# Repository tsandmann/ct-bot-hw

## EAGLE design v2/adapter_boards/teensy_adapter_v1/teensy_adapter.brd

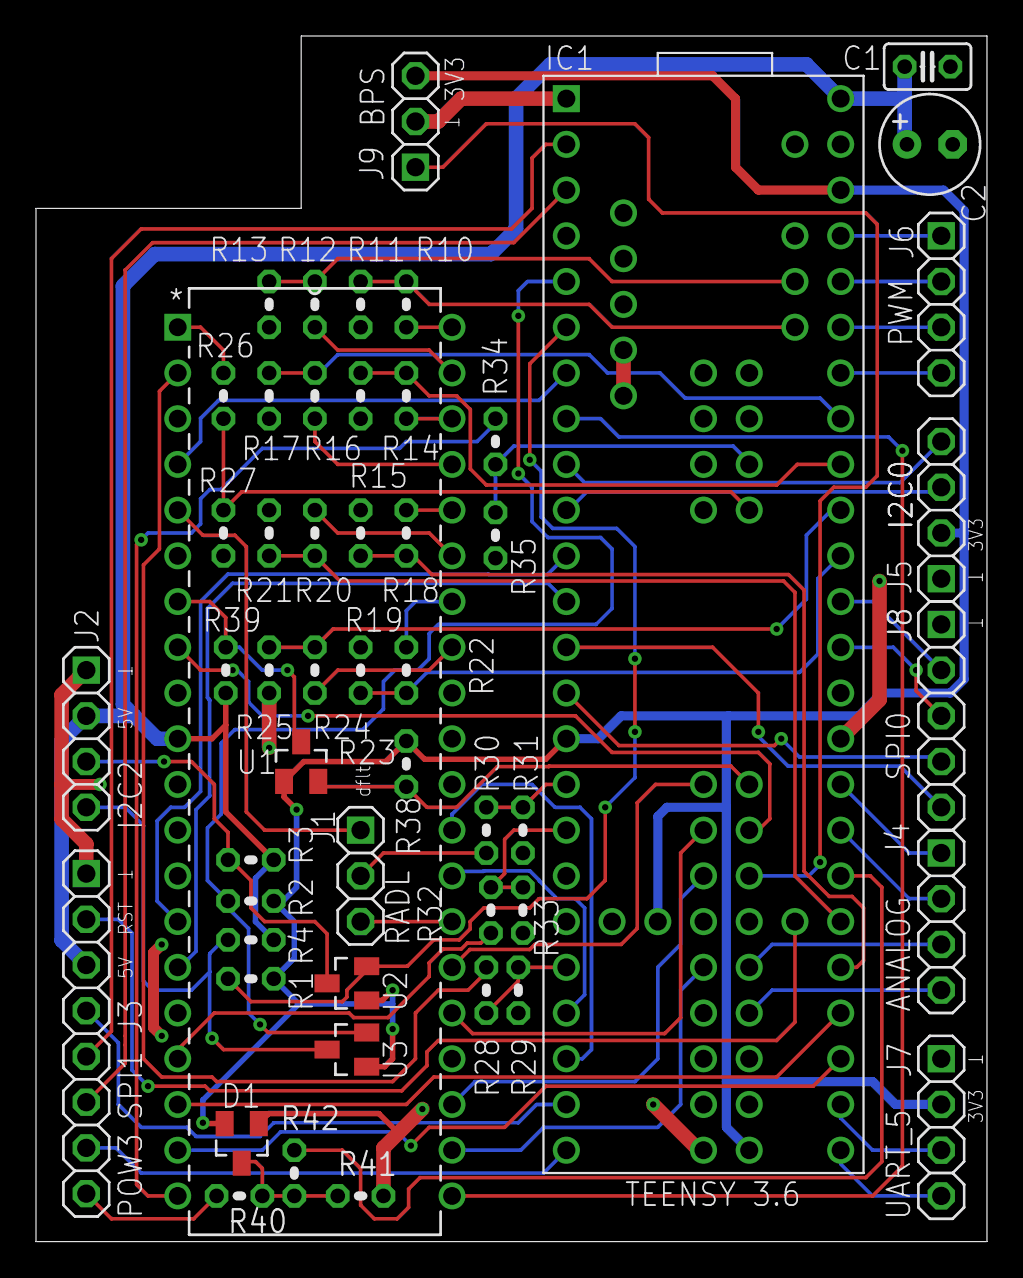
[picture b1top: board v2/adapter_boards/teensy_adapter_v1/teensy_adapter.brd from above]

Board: 2 copper layers, 52.8 x 67.0 mm, 52 parts (0 on the bottom side), 75 nets.

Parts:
C1: 100nF; C025-025X050
C2: 220uF; E2,5-6
D1: BAV99; SOT23
IC1: TEENSY 3.6; T36
IC2: ATMEGA1284P; DIP254P1524X483-40
J1: RADL; 1X03
J2: I2C_2; 1X04
J3: SPI_1; 1X08
J4: Erw_analog; 1X04
J5: I2C_0; 1X04
J6: Erw_PWM; 1X04
J7: Uart_5; 1X04
J8: SPI_0; 1X05
J9: BPS; 1X03
R1, R2, R11, R13: 4k7; 0204V
R3, R4, R38, R39: 10k; 0204V
R10, R12: 1k8; 0204V
R14, R16, R18, R20, R22, R24, R28: 0; 0204V
R15, R17, R23, R25, R26, R34, R40: 100k; 0204V
R19, R21: 820k; 0204V
R27, R35: 180k; 0204V
R29: 47k; 0204V
R30, R32: 2k2; 0204V
R31, R33: 3k9; 0204V
R41: 22k; 0204V
R42: 1k; 0204V
U1, U2, U3: BSS138

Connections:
+3V3: D1.2, IC1.3V3(1), IC1.3V3(2), IC1.3V3(3), IC1.3V3(4), J5.2, J7.2, J9.3, R1.2, R2.2, R38.1, U1.G, U2.G, U3.G
+5V: C1.1, C2.+, IC1.VIN, IC2.10, J2.2, J3.3, R3.2, R4.2, R39.1
A21_DAC0: IC1.DAC0, J4.2
A22_DAC1: IC1.DAC1, J4.1
ABSTL: IC2.40, R10.2
ABSTL_3V3: IC1.A11, R10.1, R11.1
ABSTR: IC2.39, R12.2
ABSTR_3V3: IC1.A10, R12.1, R13.1
BAT_IN_FB: IC1.39, R42.1
BPS_3V3: IC1.51, J9.1
CS0: IC1.15, J8.2
CS1: IC1.31, J3.4
CS2: IC1.43, IC2.22
FERNBED: IC2.2, R28.2
FERNBED_3V3: IC1.28, R28.1, R29.1
GND: C1.2, C2.-, D1.1, IC1.AGND, IC1.G0, IC1.G1, IC1.G2, IC1.G3, IC1.G4, IC1.G5, IC1.G6, IC2.11, IC2.31, J2.1, J3.1, J5.1, J7.1, J8.1, J9.2, R11.2, R13.2, R15.2, R17.2, R19.2, R21.2, R23.2, R25.2, R27.2, R29.2, R31.2, R33.2, R35.2, R41.2
GPIO40: IC1.40, IC2.26
GPIO41: IC1.41, IC2.25
GPIO42: IC1.42, IC2.23
KANTEL: IC2.34, R22.2
KANTEL_3V3: IC1.16, R22.1, R23.1
KANTER: IC2.33, R24.2
KANTER_3V3: IC1.17, R24.1, R25.1
KLAPPE: IC2.20, R34.2
KLAPPE_3V3: IC1.55, R34.1, R35.1
LDRL: IC2.36, R18.2
LDRL_3V3: IC1.37, R18.1, R19.1
LDRR: IC2.35, R20.2
LDRR_3V3: IC1.38, R20.1, R21.1
MAUS_CLK: IC1.52, IC2.8
MAUS_D_3V3: IC1.53, R38.2, U1.S
MISO0: IC1.12, J8.4
MISO1: IC1.1, J3.6
MLINKS: IC2.38, R14.2
MLINKS_3V3: IC1.18, R14.1, R15.1
MOSI0: IC1.11, J8.5
MOSI1: IC1.0, J3.5
MOT_L_DIR: IC1.29, IC2.28
MOT_L_PWM: IC1.35, IC2.19
MOT_R_DIR: IC1.30, IC2.29
MOT_R_PWM: IC1.36, IC2.18
MRECHTS: IC2.37, R16.2
MRECHTS_3V3: IC1.19, R16.1, R17.1
unnamed: D1.3, R40.2, R41.1, R42.2
POW3: J3.8, R40.1
PWM1: IC1.5, IC2.4
PWM2: IC1.6, IC2.21
PWM3: IC1.20, J6.4
PWM4: IC1.21, J6.3
PWM5: IC1.22, J6.2
PWM6: IC1.23, J6.1
RADL: J1.2, R30.2
RADL1: IC2.5, J1.1
RADL2: IC2.27, J1.3
RADL_3V3: IC1.24, R30.1, R31.1
RADR: IC2.17, R32.2
RADR_3V3: IC1.25, R32.1, R33.1
RESET: IC1.R, J3.2
RX2: IC1.9, IC2.14
RX5: IC1.34, J7.3
SCHRANKE: IC2.1, R26.2
SCHRANKE_3V3: IC1.54, R26.1, R27.1
SCK0: IC1.14, J8.3
SCK1: IC1.32, J3.7
SCL0: IC1.7, J5.4
SCL2: IC1.3, R2.1, U3.S
SCL2_5V: J2.4, R4.1, U3.D
SDA0: IC1.8, J5.3
SDA2: IC1.4, R1.1, U2.S
SDA2_5V: J2.3, R3.1, U2.D
SDIO_5V: IC2.7, R39.2, U1.D
SERVO2_FB: IC1.49, J4.4
SERVO3_FB: IC1.50, J4.3
TX2: IC1.10, IC2.15
TX5: IC1.33, J7.4

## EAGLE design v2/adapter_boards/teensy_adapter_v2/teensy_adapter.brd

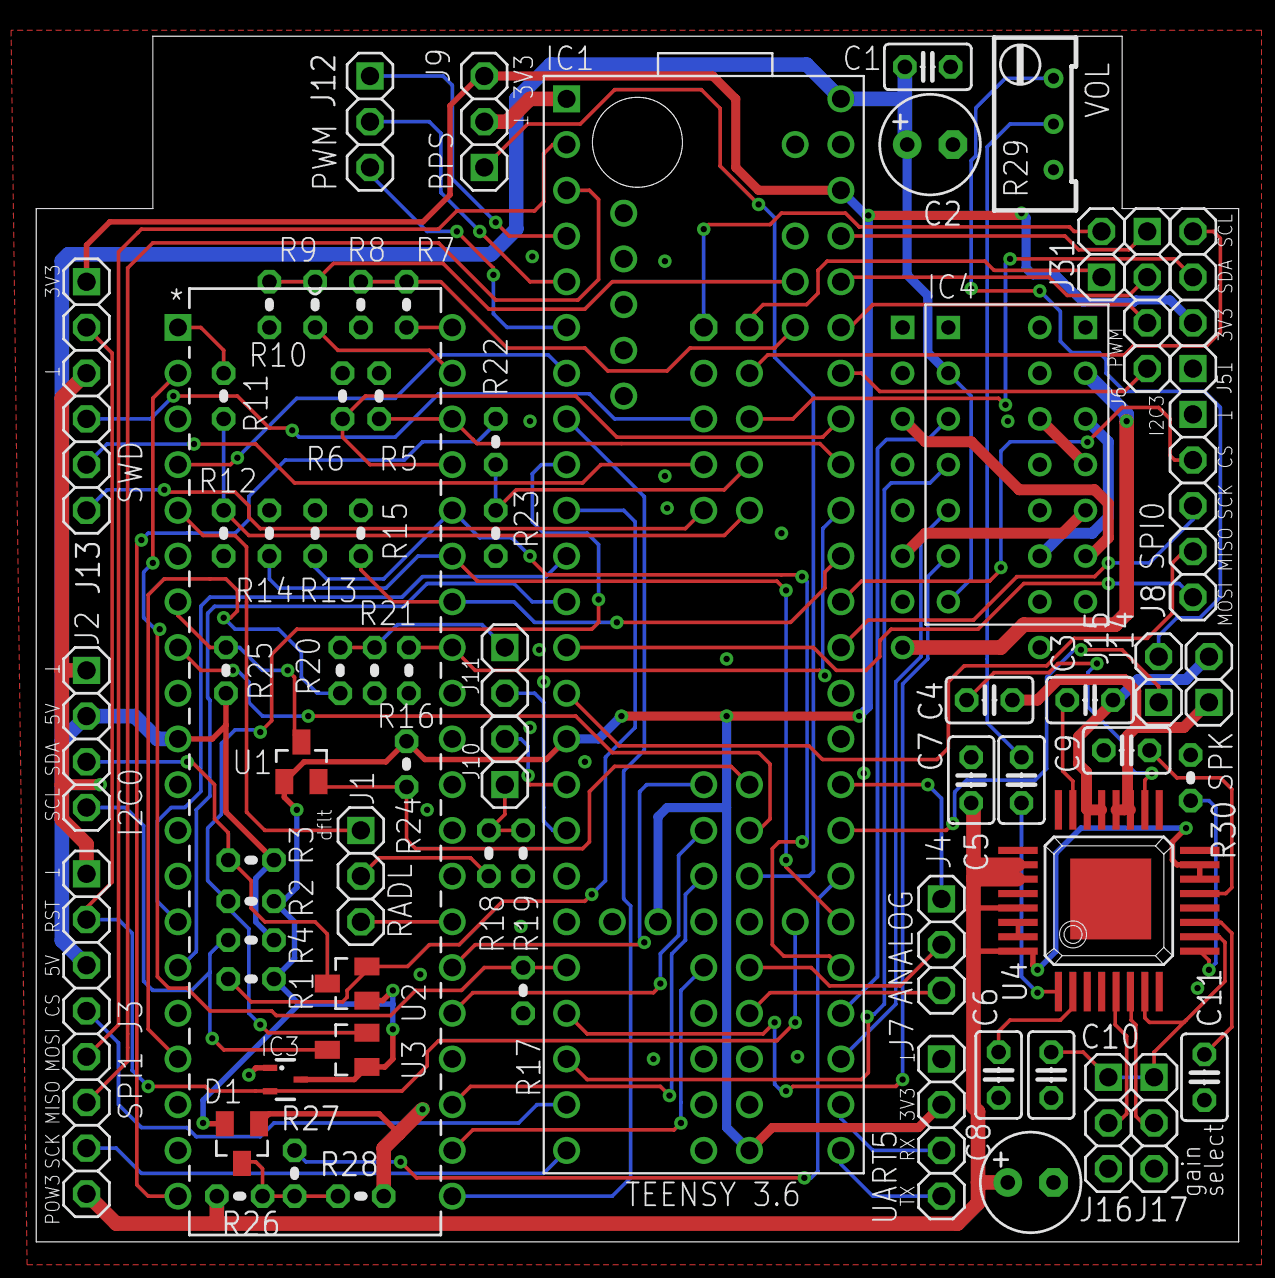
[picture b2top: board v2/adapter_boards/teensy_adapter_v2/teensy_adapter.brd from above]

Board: 2 copper layers, 66.8 x 67.0 mm, 70 parts (1 on the bottom side), 98 nets.

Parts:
C1: 100nF; C025-025X050
C2, C8: 220uF; E2,5-6
C3, C4: 220nF; C025-025X050
C5, C6, C7, C9, C11: 1uF; C025-025X050
C10: 10nF; C025-025X050
D1: BAV99; SOT23
IC1: TEENSY 3.6; T36
IC2: ATMEGA1284P; DIP254P1524X483-40
IC3: MAX803REXR; SC70-3L
IC4: DRV8835; POLOLU_MOTOR_DRV_DRV8835
IC5: L293D; DIL16
J1: RADL_SEL; 1X03
J2: I2C_0; 1X04
J3: SPI_1; 1X08
J4: Erw_analog; 1X03
J5: I2C_3; 1X04
J6: Erw_PWM_2; 1X04
J7: Uart_5; 1X04
J8: SPI_0; 1X05
J9: BPS; 1X03
J10: RADL; 1X02
J11: RADR; 1X02
J12: Erw_PWM_1; 1X03
J13: SWD; 1X06
J14: SPEAKER; 1X02
J15: AUDIO; 1X02
J16: GAIN_0; 1X03
J17: GAIN_1; 1X03
J31: SWD_KL02; 1X02
J32: SWD_KL02; 1X02/90
R1, R2, R8, R10: 4k7; 0204V
R3, R4, R24, R25: 10k; 0204V
R5, R6, R11, R15, R16, R22, R26, R30: 100k; 0204V
R7, R9: 1k8; 0204V
R12, R23: 180k; 0204V
R13, R14: 820k; 0204V
R17: 47k; 0204V
R18, R20: 2k2; 0204V
R19, R21: 3k9; 0204V
R27: 1k; 0204V
R28: 22k; 0204V
R29: 5k; RTRIM64W
U1, U2, U3: BSS138
U4: TPA3106D1; HTQFP32

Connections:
+3V3: D1.2, IC1.3V3(1), IC1.3V3(2), IC1.3V3(3), IC1.3V3(4), IC3.3, J5.2, J7.2, J9.3, J13.1, R1.2, R2.2, R24.1, U1.G, U2.G, U3.G
+5V: C1.1, C2.+, IC1.VIN, IC2.10, IC4.MODE, IC4.VCC, J2.2, J3.3, R3.2, R4.2, R25.1
+6V: IC4.VIN, IC5.8
A22_DAC1: IC1.DAC1, J4.1
ABSTL: IC2.40, R7.2
ABSTL_3V3: IC1.A11, R7.1, R8.1
ABSTR: IC2.39, R9.2
ABSTR_3V3: IC1.A10, R9.1, R10.1
AUDIO_OUT: IC1.DAC0, J15.1
BAT_IN_FB: IC1.39, R27.1
BPS_3V3: IC1.51, J9.1
BSN: C4.1, U4.18
BSP: C3.1, U4.23
CS0: IC1.15, J8.2
CS1: IC1.31, J3.4
CS2: IC1.43, IC2.22
FERNBED_3V3: IC1.28, IC2.2, R17.1
GAIN0: J16.2, U4.5
GAIN1: J17.2, U4.6
GND: C1.2, C2.-, C6.2, C7.2, C8.-, C9.2, C10.2, C11.2, D1.1, IC1.AGND, IC1.G0, IC1.G1, IC1.G2, IC1.G3, IC1.G4, IC1.G5, IC1.G6, IC2.11, IC2.31, IC3.1, IC4.LGND, IC4.MGND, J2.1, J3.1, J5.1, J7.1, J8.1, J9.2, J13.3, J16.3, J17.3, R5.2, R6.2, R8.2, R10.2, R12.2, R13.2, R14.2, R15.2, R16.2, R17.2, R19.2, R21.2, R23.2, R28.2, R29.1, R30.1, U4.3, U4.4, U4.12, U4.16, U4.17, U4.24, U4.25, U4.PAD
GPIO40: IC1.40, IC2.26
GPIO41: IC1.41, IC2.25
GPIO42: IC1.42, IC2.23
INN: C6.1, U4.2
INP: C5.1, U4.1
KANTEL_3V3: IC1.16, IC2.34, R15.1
KANTER_3V3: IC1.17, IC2.33, R16.1
KL02_DC: J31.1, J32.1
KL02_DD: J31.2, J32.2
KLAPPE: IC2.20, R22.2
KLAPPE_3V3: IC1.55, R22.1, R23.1
LDRL_3V3: IC1.37, IC2.36, R13.1
LDRR_3V3: IC1.38, IC2.35, R14.1
LINE_IN: J15.2, R29.3
MAUS_CLK: IC1.52, IC2.8
MAUS_D_3V3: IC1.53, R24.2, U1.S
MISO0: IC1.12, J8.4
MISO1: IC1.1, J3.6
MLINKS_3V3: IC1.18, IC2.38, R5.1
MOSI0: IC1.11, J8.5
MOSI1: IC1.0, J3.5
MOT_L_1: IC4.AOUT1, IC5.3
MOT_L_2: IC4.AOUT2, IC5.6
MOT_L_DIR: IC1.29, IC4.APHASE
MOT_L_PWM: IC1.35, IC4.AENBL
MOT_R_1: IC4.BOUT1, IC5.14
MOT_R_2: IC4.BOUT2, IC5.11
MOT_R_DIR: IC1.30, IC4.BPHASE
MOT_R_PWM: IC1.36, IC4.BENBL
MRECHTS_3V3: IC1.19, IC2.37, R6.1
unnamed: D1.3, R26.2, R27.2, R28.1
unnamed: U4.30, U4.31
unnamed: C5.2, R29.2
OUTN: C4.2, J14.1, U4.19, U4.20
OUTP: C3.2, J14.2, U4.21, U4.22
POW3: C7.1, C8.+, J3.8, R26.1, U4.14, U4.15, U4.26, U4.27, U4.29, U4.32
PWM1: IC1.5, IC2.4
PWM2: IC1.6, IC2.21
PWM3: IC1.20, J6.4
PWM4: IC1.21, J6.3
PWM5: IC1.22, J6.2
PWM6: IC1.23, J6.1
PWM_ERW1: IC1.2, J12.1
PWM_ERW2: IC1.3, J12.2
PWM_ERW3: IC1.4, J12.3
RADL: IC1.24, J10.2
RADL1: IC2.5, J1.1
RADL2: IC2.27, J1.3
RADL_3V3: J10.1, R18.1, R19.1
RADL_5V: J1.2, R18.2
RADR: IC1.25, J11.2
RADR_3V3: J11.1, R20.1, R21.1
RADR_5V: IC2.17, R20.2
RESET: IC1.R, IC3.2, J3.2, J13.2
ROSC: R30.2, U4.9
RX2: IC1.9, IC2.14
RX5: IC1.34, J7.3
SCHRANKE: IC2.1, R11.2
SCHRANKE_3V3: IC1.54, R11.1, R12.1
SCK0: IC1.14, J8.3
SCK1: IC1.32, J3.7
SCL0: IC1.7, R2.1, U3.S
SCL0_5V: J2.4, R4.1, U3.D
SCL3: IC1.57, J5.4
SDA0: IC1.8, R1.1, U2.S
SDA0_5V: J2.3, R3.1, U2.D
SDA3: IC1.56, J5.3
SDIO_5V: IC2.7, R25.2, U1.D
SERVO2_FB: IC1.49, J4.3
SERVO3_FB: IC1.50, J4.2
SWCLK: IC1.DC, J13.5
SWDIO: IC1.DD, J13.6
SWD_EN: IC1.DE, J13.4
TX2: IC1.10, IC2.15
TX5: IC1.33, J7.4
VBYP: C11.1, U4.11
VCLAMP: C9.1, U4.13
VREG: C10.1, J16.1, J17.1, U4.7, U4.10

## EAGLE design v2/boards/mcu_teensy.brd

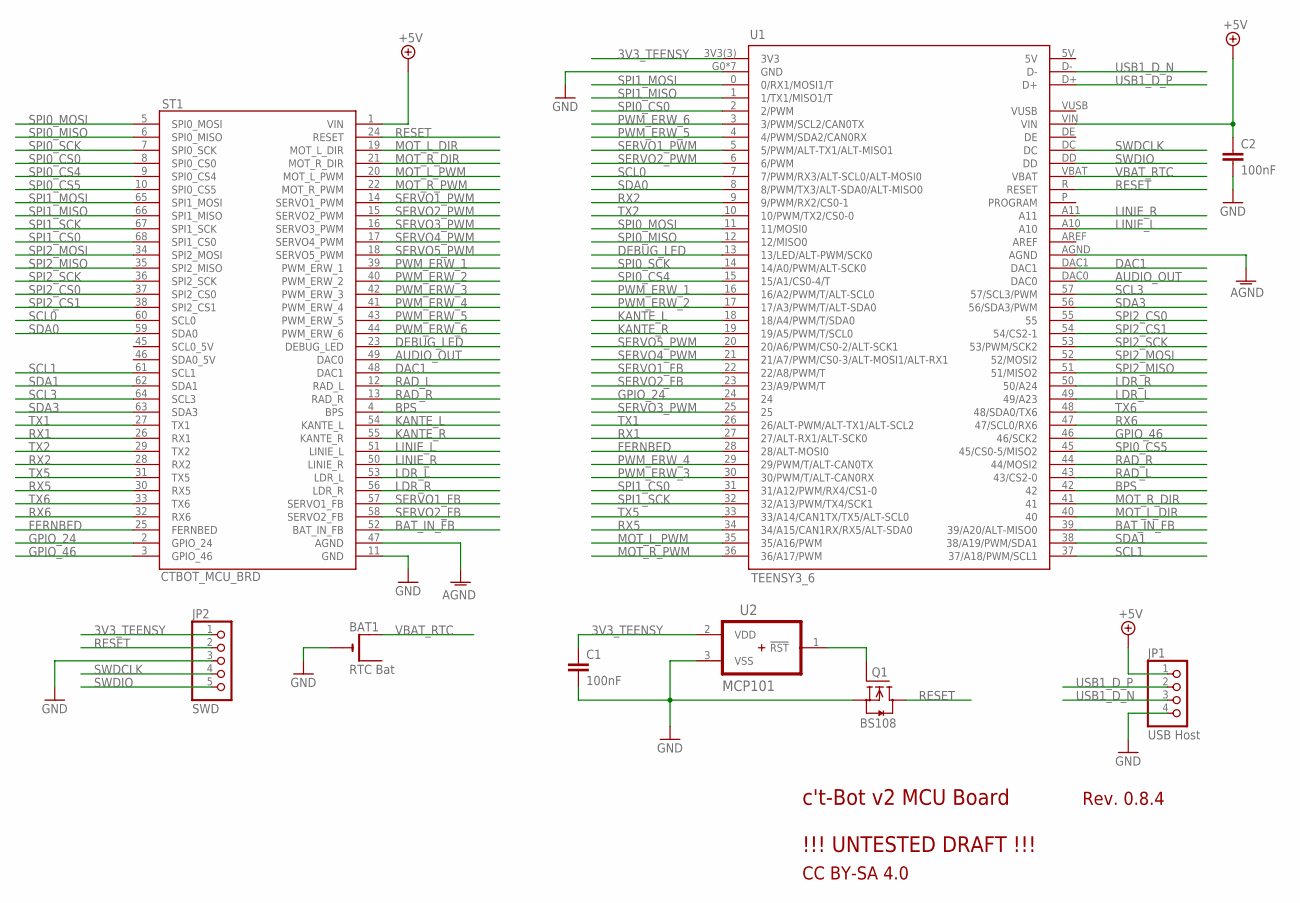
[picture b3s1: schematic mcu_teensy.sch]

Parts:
BAT1: RTC Bat; CR1220-SMD
C1, C2: 100nF; C025-025X050
JP1: USB Host; 1X04/90
JP2: SWD; 1X05/90
Q1: BS108; SOT54E
ST1: CTBOT_MCU_BRD; DIP66
U1: TEENSY3_6; T36
U2: MCP101; TO-92

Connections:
3V3_TEENSY: C1.1, JP2.1, U1.3V3(3) (3V3), U2.2 (VDD)
+5V: C2.1, JP1.1, ST1.1 (VIN), U1.VIN
AGND: ST1.47 (AGND), U1.AGND
AUDIO_OUT: ST1.49 (DAC0), U1.DAC0
BAT_IN_FB: ST1.52 (BAT_IN_FB), U1.39 (39/A20/ALT-MISO0)
BPS: ST1.4 (BPS), U1.42
DAC1: ST1.48 (DAC1), U1.DAC1
DEBUG_LED: ST1.23 (DEBUG_LED), U1.13 (13/LED/ALT-PWM/SCK0)
FERNBED: ST1.25 (FERNBED), U1.28 (28/ALT-MOSI0)
GND: BAT1.-, C1.2, C2.2, JP1.4, JP2.3, Q1.S, ST1.11 (GND), U1.G0 (GND), U1.G1 (GND), U1.G2 (GND), U1.G3 (GND), U1.G4 (GND), U1.G5 (GND), U1.G6 (GND), U2.3 (VSS)
GPIO_24: ST1.2 (GPIO_24), U1.24
GPIO_46: ST1.3 (GPIO_46), U1.46 (46/SCK2)
KANTE_L: ST1.54 (KANTE_L), U1.18 (18/A4/PWM/T/SDA0)
KANTE_R: ST1.55 (KANTE_R), U1.19 (19/A5/PWM/T/SCL0)
LDR_L: ST1.53 (LDR_L), U1.49 (49/A23)
LDR_R: ST1.56 (LDR_R), U1.50 (50/A24)
LINIE_L: ST1.51 (LINIE_L), U1.A10
LINIE_R: ST1.50 (LINIE_R), U1.A11
MOT_L_DIR: ST1.19 (MOT_L_DIR), U1.40
MOT_L_PWM: ST1.20 (MOT_L_PWM), U1.35 (35/A16/PWM)
MOT_R_DIR: ST1.21 (MOT_R_DIR), U1.41
MOT_R_PWM: ST1.22 (MOT_R_PWM), U1.36 (36/A17/PWM)
unnamed: Q1.G, U2.1 (!RST)
PWM_ERW_1: ST1.39 (PWM_ERW_1), U1.16 (16/A2/PWM/T/ALT-SCL0)
PWM_ERW_2: ST1.40 (PWM_ERW_2), U1.17 (17/A3/PWM/T/ALT-SDA0)
PWM_ERW_3: ST1.42 (PWM_ERW_3), U1.30 (30/PWM/T/ALT-CAN0RX)
PWM_ERW_4: ST1.41 (PWM_ERW_4), U1.29 (29/PWM/T/ALT-CAN0TX)
PWM_ERW_5: ST1.43 (PWM_ERW_5), U1.4 (4/PWM/SDA2/CAN0RX)
PWM_ERW_6: ST1.44 (PWM_ERW_6), U1.3 (3/PWM/SCL2/CAN0TX)
RAD_L: ST1.12 (RAD_L), U1.43 (43/CS2-0)
RAD_R: ST1.13 (RAD_R), U1.44 (44/MOSI2)
RESET: JP2.2, Q1.D, ST1.24 (RESET), U1.R (RESET)
RX1: ST1.26 (RX1), U1.27 (27/ALT-RX1/ALT-SCK0)
RX2: ST1.28 (RX2), U1.9 (9/PWM/RX2/CS0-1)
RX5: ST1.30 (RX5), U1.34 (34/A15/CAN1RX/RX5/ALT-SDA0)
RX6: ST1.32 (RX6), U1.47 (47/SCL0/RX6)
SCL0: ST1.60 (SCL0), U1.7 (7/PWM/RX3/ALT-SCL0/ALT-MOSI0)
SCL1: ST1.61 (SCL1), U1.37 (37/A18/PWM/SCL1)
SCL3: ST1.64 (SCL3), U1.57 (57/SCL3/PWM)
SDA0: ST1.59 (SDA0), U1.8 (8/PWM/TX3/ALT-SDA0/ALT-MISO0)
SDA1: ST1.62 (SDA1), U1.38 (38/A19/PWM/SDA1)
SDA3: ST1.63 (SDA3), U1.56 (56/SDA3/PWM)
SERVO1_FB: ST1.57 (SERVO1_FB), U1.22 (22/A8/PWM/T)
SERVO1_PWM: ST1.14 (SERVO1_PWM), U1.5 (5/PWM/ALT-TX1/ALT-MISO1)
SERVO2_FB: ST1.58 (SERVO2_FB), U1.23 (23/A9/PWM/T)
SERVO2_PWM: ST1.15 (SERVO2_PWM), U1.6 (6/PWM)
SERVO3_PWM: ST1.16 (SERVO3_PWM), U1.25
SERVO4_PWM: ST1.17 (SERVO4_PWM), U1.21 (21/A7/PWM/CS0-3/ALT-MOSI1/ALT-RX1)
SERVO5_PWM: ST1.18 (SERVO5_PWM), U1.20 (20/A6/PWM/CS0-2/ALT-SCK1)
SPI0_CS0: ST1.8 (SPI0_CS0), U1.2 (2/PWM)
SPI0_CS4: ST1.9 (SPI0_CS4), U1.15 (15/A1/CS0-4/T)
SPI0_CS5: ST1.10 (SPI0_CS5), U1.45 (45/CS0-5/MISO2)
SPI0_MISO: ST1.6 (SPI0_MISO), U1.12 (12/MISO0)
SPI0_MOSI: ST1.5 (SPI0_MOSI), U1.11 (11/MOSI0)
SPI0_SCK: ST1.7 (SPI0_SCK), U1.14 (14/A0/PWM/ALT-SCK0)
SPI1_CS0: ST1.68 (SPI1_CS0), U1.31 (31/A12/PWM/RX4/CS1-0)
SPI1_MISO: ST1.66 (SPI1_MISO), U1.1 (1/TX1/MISO1/T)
SPI1_MOSI: ST1.65 (SPI1_MOSI), U1.0 (0/RX1/MOSI1/T)
SPI1_SCK: ST1.67 (SPI1_SCK), U1.32 (32/A13/PWM/TX4/SCK1)
SPI2_CS0: ST1.37 (SPI2_CS0), U1.55
SPI2_CS1: ST1.38 (SPI2_CS1), U1.54 (54/CS2-1)
SPI2_MISO: ST1.35 (SPI2_MISO), U1.51 (51/MISO2)
SPI2_MOSI: ST1.34 (SPI2_MOSI), U1.52 (52/MOSI2)
SPI2_SCK: ST1.36 (SPI2_SCK), U1.53 (53/PWM/SCK2)
SWDCLK: JP2.4, U1.DC
SWDIO: JP2.5, U1.DD
TX1: ST1.27 (TX1), U1.26 (26/ALT-PWM/ALT-TX1/ALT-SCL2)
TX2: ST1.29 (TX2), U1.10 (10/PWM/TX2/CS0-0)
TX5: ST1.31 (TX5), U1.33 (33/A14/CAN1TX/TX5/ALT-SCL0)
TX6: ST1.33 (TX6), U1.48 (48/SDA0/TX6)
USB1_D_N: JP1.3, U1.D-
USB1_D_P: JP1.2, U1.D+
VBAT_RTC: BAT1.+$1 (+), U1.VBAT

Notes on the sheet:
c't-Bot v2 MCU Board !!! UNTESTED DRAFT !!!
Rev. 0.8.4
CC BY-SA 4.0

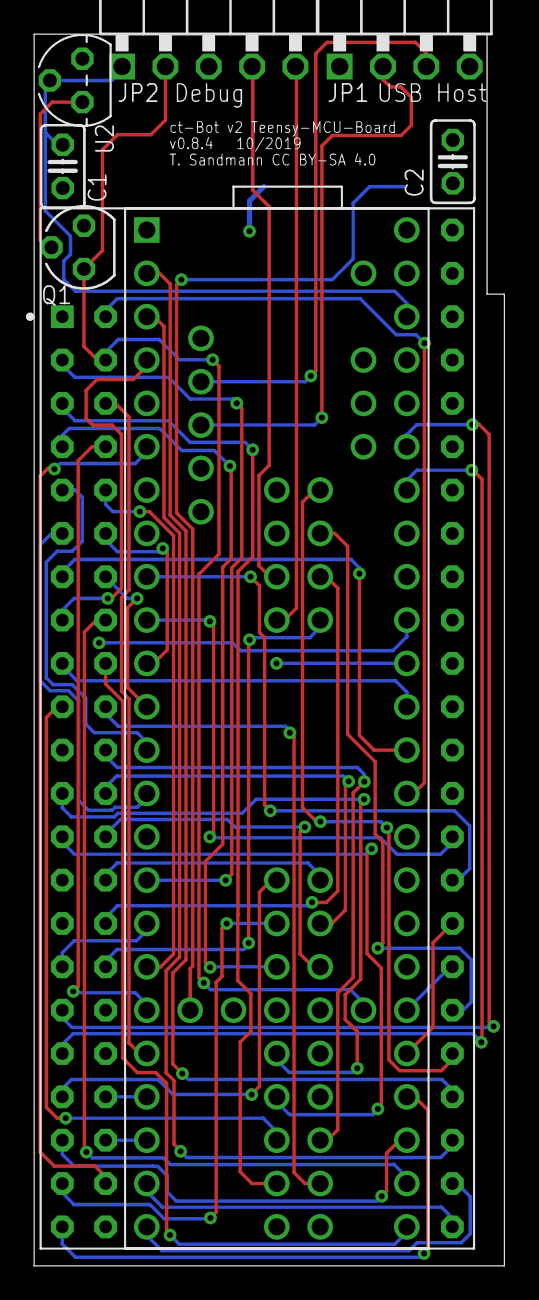
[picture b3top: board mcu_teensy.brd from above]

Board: 4 copper layers, 27.6 x 72.2 mm, 9 parts (1 on the bottom side), 73 nets.

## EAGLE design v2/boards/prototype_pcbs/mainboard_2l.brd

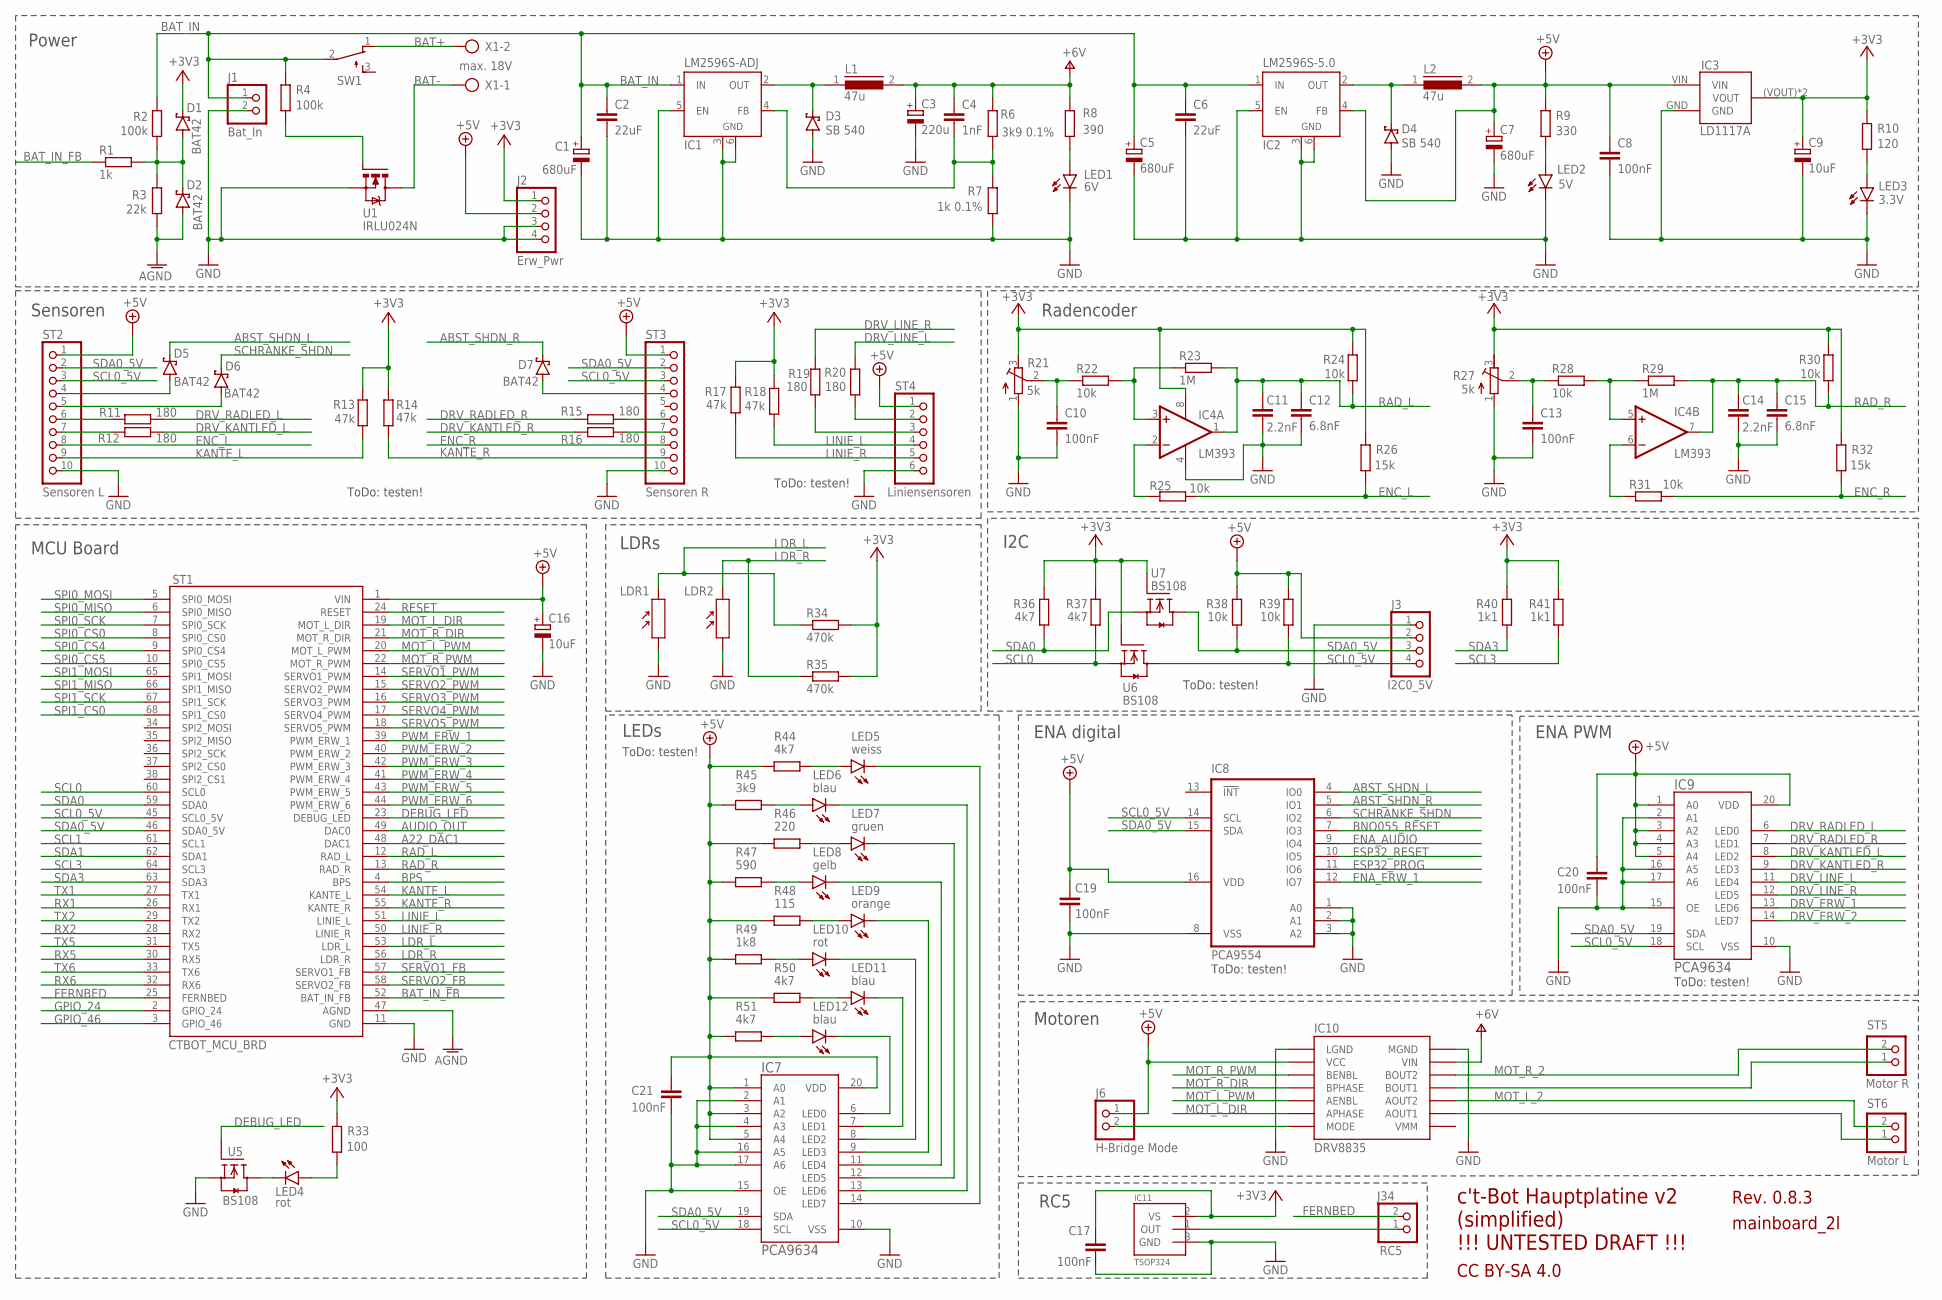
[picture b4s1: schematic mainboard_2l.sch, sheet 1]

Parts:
C1, C5, C7: 680uF; E5-10,5
C2, C6: 22uF; C025-025X050
C3: 220u; E5-10,5
C4: 1nF; C025-025X050
C8, C10, C13, C17, C19, C20, C21: 100nF; C025-025X050
C9: 10uF; E2-5
C11, C14: 2.2nF; C025-025X050
C12, C15: 6.8nF; C025-025X050
C16: 10uF; TT2D5L
D1, D2: BAT42; DO35-7
D3, D4: SB 540; DO201T15
D5, D6, D7: BAT42; 0207/2V
IC1: LM2596S-ADJ; TO263-5
IC2: LM2596S-5.0; TO263-5
IC3: LD1117A; LD1117SOT-223
IC4: LM393; DIL08
IC7, IC9: PCA9634; SO20W
IC8: PCA9554; SO16W
IC10: DRV8835
IC11: TSOP324
J1: Bat_In; 1X02
J2: Erw_Pwr; 1X04
J3: I2C0_5V; 1X04
J6: H-Bridge Mode; 1X02
J34: RC5; 1X02
L1, L2: 47u; 09HCP
LDR1, LDR2: MPY54C569; SNR2-3.0
LED1: 6V; LED3MM
LED2: 5V; LED3MM
LED3: 3.3V; LED3MM
LED4, LED10: rot; LED3MM
LED5: weiss; LED3MM
LED6, LED11, LED12: blau; LED3MM
LED7: gruen; LED3MM
LED8: gelb; LED3MM
LED9: orange; LED3MM
R1: 1k; 0204/7
R2, R4: 100k; 0204V
R3: 22k; 0204/7
R6: 3k9 0.1%; 0204V
R7: 1k 0.1%; 0204V
R8: 390; 0204V
R9: 330; 0204V
R10: 120; 0204V
R11, R12, R15, R16, R19, R20: 180; 0204V
R13, R14, R17, R18: 47k; 0204V
R21, R27: 5k; RTRIM64W
R22, R24, R25, R31, R38, R39: 10k; 0204V
R23: 1M; 0204V
R26, R32: 15k; 0204V
R28, R30: 10k; 0204/7
R29: 1M; 0204/7
R33: 100; 0204V
R34, R35: 470k; 0204V
R36, R37, R44, R50, R51: 4k7; 0204V
R40, R41: 1k1; 0204V
R45: 3k9; 0204V
R46: 220; 0204V
R47: 590; 0204V
R48: 115; 0204V
R49: 1k8; 0204V
ST1: CTBOT_MCU_BRD; DIP66
ST2: Sensoren L; TS_PS25_10
ST3: Sensoren R; TS_PS25_10
ST4: Liniensensoren; TS_PS25_6
ST5: Motor R; 1X02/90
ST6: Motor L; 1X02/90
SW1: TL32PO; TL3XPO
U1: IRLU024N; TO251AA
U5, U6, U7: BS108; SOT54E
X1: max. 18V; AK500/2-H

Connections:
+3V3: C9.+, C17.1, D1.C, IC3.(VOUT) (VOUT), IC3.VOUT, IC4.8 (V+), IC11.2 (VS), J2.1, R10.2, R13.2, R14.1, R17.2, R18.2, R21.3 (E), R24.2, R26.2, R27.3 (E), R30.2, R32.2, R33.2, R34.2, R35.2, R36.2, R37.2, R40.2, R41.2, U6.G, U7.G; also elsewhere on the board
+6V: C3.+, C4.1, IC10.VIN, L1.2, R6.2, R8.1; also elsewhere on the board
A22_DAC1: ST1.48 (DAC1); also elsewhere on the board
ABST_SHDN_L: D5.2 (C), IC8.4 (IO0)
ABST_SHDN_R: D7.2 (C), IC8.5 (IO1)
AGND: D2.A, R3.1, ST1.47 (AGND); also elsewhere on the board
AUDIO_OUT: ST1.49 (DAC0); also elsewhere on the board
BAT+: SW1.1 (O), X1.2
BAT-: U1.2 (D), U1.4 (D), X1.1
BAT_IN: C1.+, C2.1, C5.+, C6.1, IC1.1 (IN), IC2.1 (IN), J1.1, R2.2, R4.2, SW1.2
BAT_IN_FB: R1.1, ST1.52 (BAT_IN_FB)
BNO055_RESET: IC8.7 (IO3); also elsewhere on the board
BPS: ST1.4 (BPS); also elsewhere on the board
DEBUG_LED: ST1.23 (DEBUG_LED), U5.G
DRV_ERW_1: IC9.13 (LED6); also elsewhere on the board
DRV_ERW_2: IC9.14 (LED7); also elsewhere on the board
DRV_KANTLED_L: IC9.8 (LED2), R12.2
DRV_KANTLED_R: IC9.9 (LED3), R16.1
DRV_LINE_L: IC9.11 (LED4), R20.2
DRV_LINE_R: IC9.12 (LED5), R19.2
DRV_RADLED_L: IC9.6 (LED0), R11.2
DRV_RADLED_R: IC9.7 (LED1), R15.1
ENA_AUDIO: IC8.9 (IO4); also elsewhere on the board
ENA_ERW_1: IC8.12 (IO7); also elsewhere on the board
ENC_L: R25.2, R26.1, ST2.8
ENC_R: R31.2, R32.1, ST3.8
ESP32_PROG: IC8.11 (IO6); also elsewhere on the board
ESP32_RESET: IC8.10 (IO5); also elsewhere on the board
FERNBED: J34.2, ST1.25 (FERNBED)
GND: C1.-, C2.2, C3.-, C5.-, C6.2, C7.-, C8.2, C9.-, C10.2, C11.2, C12.2, C13.2, C14.2, C15.2, C16.-, C17.2, C19.2, C20.2, C21.2, D3.A, D4.A, IC1.3 (GND), IC1.5 (EN), IC1.6 (GND), IC2.3 (GND), IC2.5 (EN), IC2.6 (GND), IC3.GND, IC4.4 (V-), IC7.2 (A1), IC7.4 (A3), IC7.10 (VSS), IC7.15 (OE), IC7.16 (A5), IC7.17 (A6), IC8.1 (A0), IC8.2 (A1), IC8.3 (A2), IC8.8 (VSS), IC9.2 (A1), IC9.10 (VSS), IC9.15 (OE), IC9.16 (A5), IC9.17 (A6), IC10.LGND, IC10.MGND, IC11.3 (GND), J1.2, J2.3, J2.4, J3.1, LDR1.1, LDR2.1, LED1.K (C), LED2.K (C), LED3.K (C), R7.1, R21.1 (A), R27.1 (A), ST1.11 (GND), ST2.10, ST3.10, ST4.6, U1.3 (S), U5.S; also elsewhere on the board
GPIO_24: ST1.2 (GPIO_24); also elsewhere on the board
GPIO_46: ST1.3 (GPIO_46); also elsewhere on the board
KANTE_L: R13.1, ST1.54 (KANTE_L), ST2.9
KANTE_R: R14.2, ST1.55 (KANTE_R), ST3.9
LDR_L: LDR1.2, R34.1, ST1.53 (LDR_L)
LDR_R: LDR2.2, R35.1, ST1.56 (LDR_R)
LINIE_L: R18.1, ST1.51 (LINIE_L), ST4.4
LINIE_R: R17.1, ST1.50 (LINIE_R), ST4.5
MOT_L_1: IC10.AOUT1, ST6.1
MOT_L_2: IC10.AOUT2, ST6.2
MOT_L_DIR: IC10.APHASE, ST1.19 (MOT_L_DIR)
MOT_L_PWM: IC10.AENBL, ST1.20 (MOT_L_PWM)
MOT_R_1: IC10.BOUT1, ST5.1
MOT_R_2: IC10.BOUT2, ST5.2
MOT_R_DIR: IC10.BPHASE, ST1.21 (MOT_R_DIR)
MOT_R_PWM: IC10.BENBL, ST1.22 (MOT_R_PWM)
unnamed: R19.1, ST4.3
unnamed: LED3.A, R10.1
unnamed: IC10.MODE, J6.2
unnamed: D1.A, D2.C, R1.2, R2.1, R3.2
unnamed: IC4.2 (-IN), R25.1
unnamed: IC7.6 (LED0), LED12.K (C)
unnamed: IC7.7 (LED1), LED11.K (C)
unnamed: LED1.A, R8.2
unnamed: C4.2, IC1.4 (FB), R6.1, R7.2
unnamed: IC4.6 (-IN), R31.1
unnamed: LED2.A, R9.1
unnamed: IC7.8 (LED2), LED10.K (C)
unnamed: IC7.9 (LED3), LED9.K (C)
unnamed: IC7.11 (LED4), LED8.K (C)
unnamed: IC7.12 (LED5), LED7.K (C)
unnamed: IC7.13 (LED6), LED6.K (C)
unnamed: IC7.14 (LED7), LED5.K (C)
unnamed: LED5.A, R44.2
unnamed: LED6.A, R45.2
unnamed: LED7.A, R46.2
unnamed: LED8.A, R47.2
unnamed: LED9.A, R48.2
unnamed: LED10.A, R49.2
unnamed: LED11.A, R50.2
unnamed: LED12.A, R51.2
unnamed: LED4.A, R33.1
unnamed: LED4.K (C), U5.D
unnamed: R20.1, ST4.2
unnamed: C10.1, R21.2 (S), R22.1
unnamed: IC4.3 (+IN), R22.2, R23.1
unnamed: C13.1, R27.2 (S), R28.1
unnamed: IC4.5 (+IN), R28.2, R29.1
unnamed: R4.1, U1.1 (G)
unnamed: R15.2, ST3.6
unnamed: R11.1, ST2.6
unnamed: R12.1, ST2.7
unnamed: R16.2, ST3.7
PWM_ERW_1: ST1.39 (PWM_ERW_1)
PWM_ERW_2: ST1.40 (PWM_ERW_2)
PWM_ERW_3: ST1.42 (PWM_ERW_3); also elsewhere on the board
PWM_ERW_4: ST1.41 (PWM_ERW_4)
PWM_ERW_5: ST1.43 (PWM_ERW_5)
PWM_ERW_6: ST1.44 (PWM_ERW_6)
RAD_L: C11.1, C12.1, IC4.1 (OUT), R23.2, R24.1, ST1.12 (RAD_L)
RAD_R: C14.1, C15.1, IC4.7 (OUT), R29.2, R30.1, ST1.13 (RAD_R)
RC5: IC11.1 (OUT), J34.1
RESET: ST1.24 (RESET); also elsewhere on the board
RX1: ST1.26 (RX1); also elsewhere on the board
RX2: ST1.28 (RX2)
RX5: ST1.30 (RX5); also elsewhere on the board
RX6: ST1.32 (RX6); also elsewhere on the board
SCHRANKE_SHDN: D6.2 (C), IC8.6 (IO2)
SCL0: R37.1, ST1.60 (SCL0), U6.S; also elsewhere on the board
SCL0_5V: IC7.18 (SCL), IC8.14 (SCL), IC9.18 (SCL), J3.4, R39.1, ST1.45 (SCL0_5V), ST2.3, ST3.3, U6.D; also elsewhere on the board
SCL1: ST1.61 (SCL1)
SCL3: R41.1, ST1.64 (SCL3); also elsewhere on the board
SDA0: R36.1, ST1.59 (SDA0), U7.S; also elsewhere on the board
SDA0_5V: IC7.19 (SDA), IC8.15 (SDA), IC9.19 (SDA), J3.3, R38.1, ST1.46 (SDA0_5V), ST2.2, ST3.2, U7.D; also elsewhere on the board
SDA1: ST1.62 (SDA1)
SDA3: R40.1, ST1.63 (SDA3); also elsewhere on the board
SERVO1_FB: ST1.57 (SERVO1_FB); also elsewhere on the board
SERVO1_PWM: ST1.14 (SERVO1_PWM); also elsewhere on the board
SERVO2_FB: ST1.58 (SERVO2_FB)
SERVO2_PWM: ST1.15 (SERVO2_PWM)
SERVO3_PWM: ST1.16 (SERVO3_PWM)
SERVO4_PWM: ST1.17 (SERVO4_PWM); also elsewhere on the board
SERVO5_PWM: ST1.18 (SERVO5_PWM); also elsewhere on the board
SPI0_CS0: ST1.8 (SPI0_CS0); also elsewhere on the board
SPI0_CS4: ST1.9 (SPI0_CS4); also elsewhere on the board
SPI0_CS5: ST1.10 (SPI0_CS5); also elsewhere on the board
SPI0_MISO: ST1.6 (SPI0_MISO); also elsewhere on the board
SPI0_MOSI: ST1.5 (SPI0_MOSI); also elsewhere on the board
SPI0_SCK: ST1.7 (SPI0_SCK); also elsewhere on the board
SPI1_CS0: ST1.68 (SPI1_CS0); also elsewhere on the board
SPI1_MISO: ST1.66 (SPI1_MISO); also elsewhere on the board
SPI1_MOSI: ST1.65 (SPI1_MOSI); also elsewhere on the board
SPI1_SCK: ST1.67 (SPI1_SCK); also elsewhere on the board
TX1: ST1.27 (TX1); also elsewhere on the board
TX2: ST1.29 (TX2)
TX5: ST1.31 (TX5); also elsewhere on the board
TX6: ST1.33 (TX6); also elsewhere on the board
V5_L1: D4.C, IC2.2 (OUT), L2.1
V6_L1: D3.C, IC1.2 (OUT), L1.1
VCC: C7.+, C8.1, C16.+, C19.1, C20.1, C21.1, IC2.4 (FB), IC3.VIN, IC7.1 (A0), IC7.3 (A2), IC7.5 (A4), IC7.20 (VDD), IC8.16 (VDD), IC9.1 (A0), IC9.3 (A2), IC9.4 (A3), IC9.5 (A4), IC9.20 (VDD), IC10.VCC, J2.2, J3.2, J6.1, L2.2, R9.2, R38.2, R39.2, R44.1, R45.1, R46.1, R47.1, R48.1, R49.1, R50.1, R51.1, ST1.1 (VIN), ST2.1, ST3.1, ST4.1; also elsewhere on the board
VL53L0X_SHUT_L: D5.1 (A), ST2.4
VL53L0X_SHUT_R: D7.1 (A), ST3.4
VL6180X_SHDN: D6.1 (A), ST2.5

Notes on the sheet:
c't-Bot Hauptplatine v2 (simplified) !!! UNTESTED DRAFT !!!
Rev. 0.8.3
CC BY-SA 4.0
mainboard_2l
ToDo: testen!
Power
Radencoder
Sensoren
I2C
MCU Board
ENA digital
ENA PWM
Motoren
LEDs
LDRs
RC5

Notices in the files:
v2/adapter_boards/teensy_adapter_v2/teensy_adapter.brd:
CC BY-SA 11/2018
v2/boards/mcu_teensy.brd:
T. Sandmann CC BY-SA 4.0
v2/boards/mcu_teensy.sch:
c't-Bot v2 MCU Board; CC BY-SA 4.0, Timo Sandmann
v2/boards/prototype_pcbs/mainboard_2l.sch:
c't-Bot Hauptplatine v2; CC BY-SA 4.0, Timo Sandmann
